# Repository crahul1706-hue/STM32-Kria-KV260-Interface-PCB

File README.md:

# STM32 – AMD Kria KV260 Interface PCB

**A Four-Layer PCB Design for STM32F103C8T6 and AMD Kria KV260 Interfacing**

## Project Overview

This project focuses on designing a four-layer PCB interface between an STM32F103C8T6 microcontroller and the AMD Kria KV260 development platform.

The board is designed to provide communication and GPIO interfacing through SPI, UART and general-purpose digital signals using a Pmod-style connector.

The PCB schematic, component footprints, routing, copper layers and manufacturing output files were developed using KiCad 10.0.

## Key Features

- STM32F103C8T6 microcontroller interface
- Four-layer PCB architecture
- SPI communication interface
- UART debugging interface
- GPIO signal interfacing
- SWD programming and debugging connector
- External regulated 3.3V power input
- Dedicated ground plane
- PCB layout and 3D visualization
- Gerber and drill file generation

## Hardware Architecture

**Main Controller:** STM32F103C8T6

**Target Platform:** AMD Kria KV260

**Communication Interfaces:**
- SPI – SCK, MOSI, MISO and CS
- UART – TX and RX
- GPIO – FPGA_GPIO1, FPGA_GPIO2, FPGA_INT and FPGA_RESET
- SWD – Programming and debugging

## PCB Design Specifications

| Parameter | Specification |
|---|---|
| Design Tool | KiCad 10.0 |
| Microcontroller | STM32F103C8T6 |
| PCB Layers | 4 |
| Board Material | FR4 |
| Board Thickness | 1.6 mm |
| Copper Layers | F.Cu, In1.Cu, In2.Cu, B.Cu |
| Power Input | External regulated 3.3V |
| Ground Plane | In1.Cu |
| Main Communication | SPI and UART |

## Tools Used

- KiCad 10.0 – Schematic capture and PCB layout
- KiCad 3D Viewer – PCB visualization
- KiCad Design Rules Checker – PCB design verification
- Gerber Plot – Manufacturing file generation

## Repository Structure

```text
STM32-Kria-KV260-Interface-PCB/
│
├── README.md
├── Schematic/
├── PCB_Design/
│   ├── Gerber_Files/
│   └── PCB_Project/
├── Documentation/
└── Images/
```

## Project Status

**Work in Progress (WIP)**

- Schematic design completed.
- Four-layer PCB stackup configured.
- Component placement and initial routing completed.
- 3D PCB model generated.
- Gerber and drill files generated.
- Initial DRC completed with zero reported violations and zero unconnected items.
- Hardware validation and communication testing are pending.

The current design is intended for educational, portfolio and engineering documentation purposes. It has not been fabricated or hardware-validated.

## Future Improvements

- Verify KV260 Pmod pin assignments against official hardware documentation.
- Perform hardware testing after fabrication.
## Project Gallery

### PCB Layout

### 3D PCB View

###  Schematic Design and ERC Results

### 2. PCB Layout and DRC Results

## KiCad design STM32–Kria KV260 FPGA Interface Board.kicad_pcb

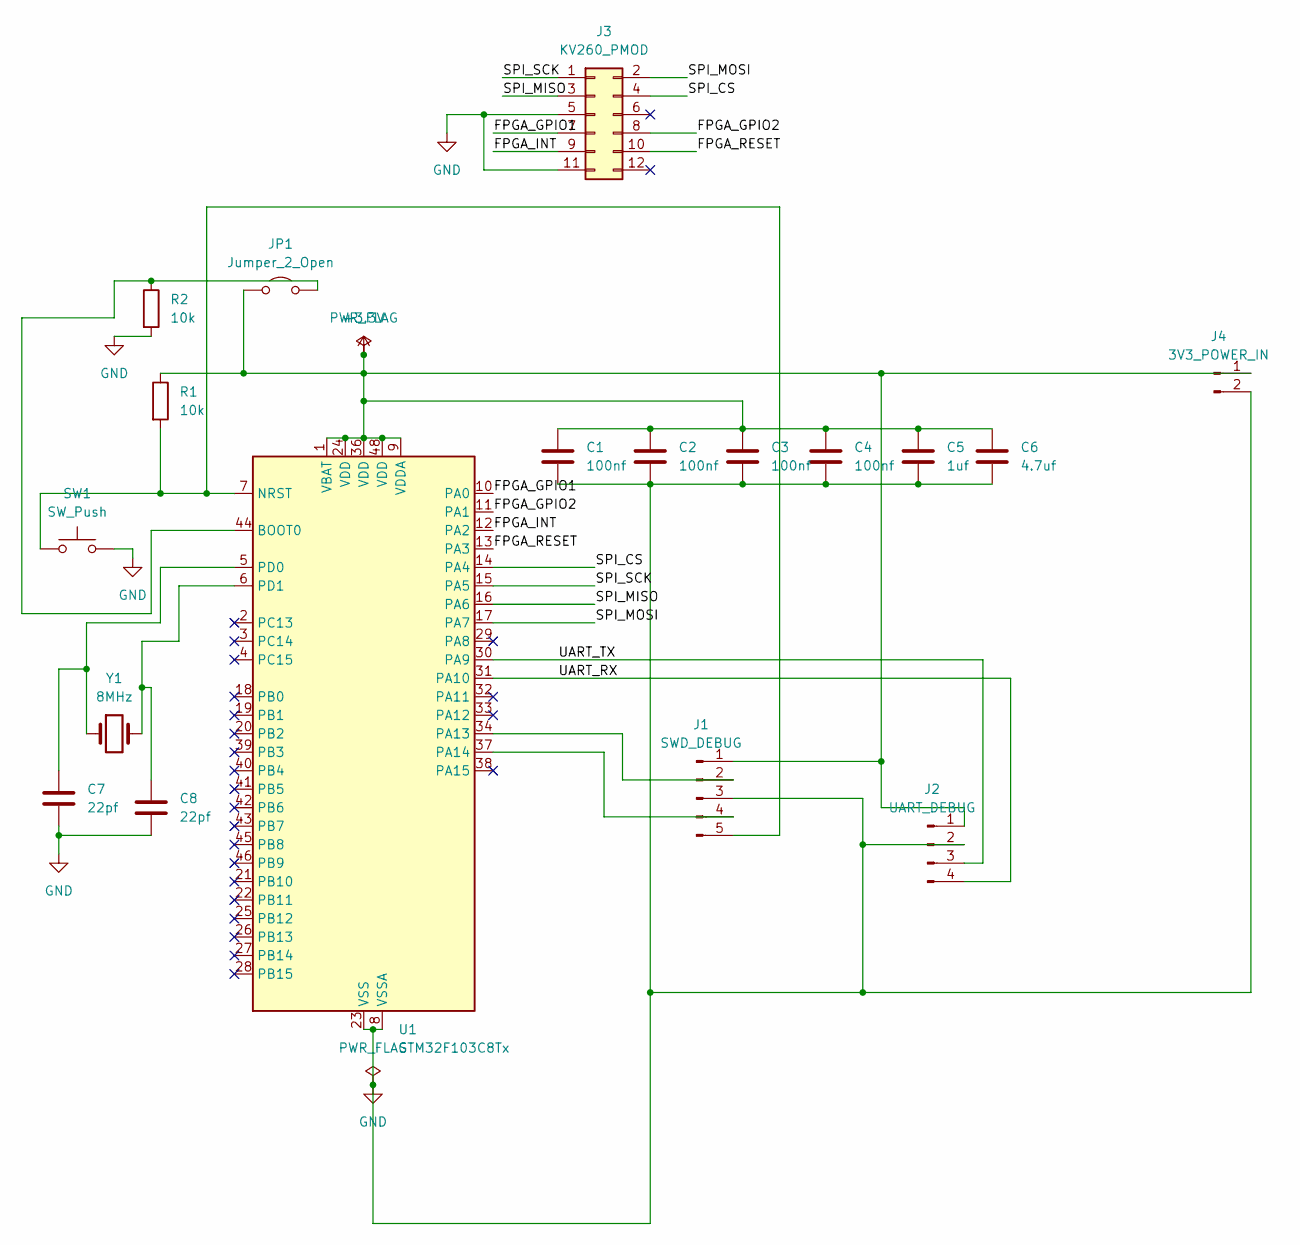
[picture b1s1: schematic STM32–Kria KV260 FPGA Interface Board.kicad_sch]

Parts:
C1, C2, C3, C4: 100nf; C_0603_1608Metric
C5: 1uf; C_0603_1608Metric
C6: 4.7uf; C_0603_1608Metric
C7, C8: 22pf; C_0603_1608Metric
J1: SWD_DEBUG; PinHeader_1x05_P2.54mm_Vertical
J2: UART_DEBUG; PinHeader_1x04_P2.54mm_Vertical
J3: KV260_PMOD; PinHeader_2x06_P2.54mm_Vertical
J4: 3V3_POWER_IN
JP1: Jumper_2_Open; SolderJumper-2_P1.3mm_Open_Pad1.0x1.5mm
R1, R2: 10k; R_0603_1608Metric
SW1: SW_Push; SW_SPST_TL3305A
U1: STM32F103C8Tx; LQFP-48_7x7mm_P0.5mm
Y1: 8MHz; Crystal_SMD_3225-4Pin_3.2x2.5mm

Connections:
+3.3V: C1.1, C2.1, C3.1, C4.1, C5.1, C6.1, J1.1, J2.1, J4.1, JP1.1 (A), R1.1, U1.1 (VBAT), U1.9 (VDDA), U1.24 (VDD), U1.36 (VDD), U1.48 (VDD)
/FPGA_GPIO1: J3.7, U1.10 (PA0)
/FPGA_GPIO2: J3.8, U1.11 (PA1)
/FPGA_INT: J3.9, U1.12 (PA2)
/FPGA_RESET: J3.10, U1.13 (PA3)
/SPI_CS: J3.4, U1.14 (PA4)
/SPI_MISO: J3.3, U1.16 (PA6)
/SPI_MOSI: J3.2, U1.17 (PA7)
/SPI_SCK: J3.1, U1.15 (PA5)
/UART_RX: J2.4, U1.31 (PA10)
/UART_TX: J2.3, U1.30 (PA9)
GND: C1.2, C2.2, C3.2, C4.2, C5.2, C6.2, C7.2, C8.2, J1.3, J2.2, J3.5, J3.11, J4.2, R2.2, SW1.2, U1.8 (VSSA), U1.23 (VSS), U1.35 (VSS), U1.47 (VSS)
unnamed: J1.2, U1.34 (PA13)
unnamed: J1.4, U1.37 (PA14)
unnamed: J1.5, R1.2, SW1.1, U1.7 (NRST)
unnamed: JP1.2 (B), R2.1, U1.44 (BOOT0)
unnamed: C7.1, U1.5 (PD0), Y1.1
unnamed: C8.1, U1.6 (PD1), Y1.2

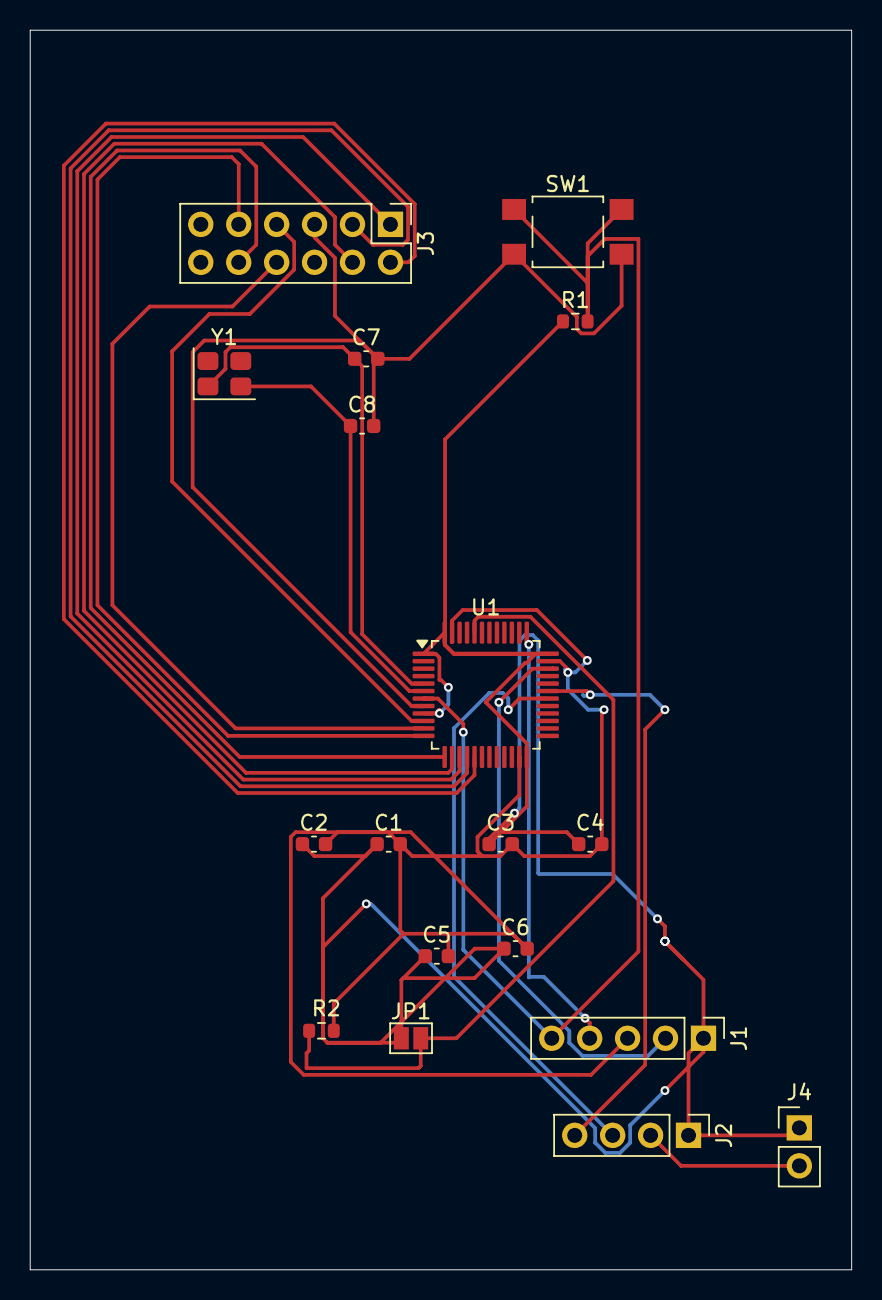
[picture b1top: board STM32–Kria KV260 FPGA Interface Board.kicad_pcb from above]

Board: 4 copper layers, 55.0 x 83.0 mm, 18 parts (0 on the bottom side), 18 nets.
